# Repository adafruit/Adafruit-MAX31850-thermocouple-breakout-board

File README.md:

# PCB files for Adafruit MAX31850 1-Wire Thermocouple Breakout Board

<a href="http://www.adafruit.com/products/1727"><br/>Click here to purchase one from the Adafruit shop</a>

Thermocouples are very sensitive, requiring a good amplifier with a cold-compensation reference. [So far we've carried the very nice MAX31855 which is an SPI interface thermocouple amplifier](https://www.adafruit.com/products/269). The '855 is great but if you have a lot of thermocouples to measure it isn't terribly easy to use. That's why we are also carrying the new '850 model from Maxim - it's a "1-Wire" thermocouple amp which can have any number of breakouts on a single shared I/O line.

The MAX31850K does everything for you, and can be easily interfaced with any microcontroller that has 1-Wire support. This breakout board has the chip itself, a 3.3V regulator with 10uF bypass capacitors all assembled and tested. This board can be used with 'parasitic power' - where the power is on the data line - or with 'local power' where the power for the converter comes in on the Vin Pin.

Please note: this board does not have level shifting on the 3V Data line - we did this on purpose so that it can be used in parasitic mode. The data line must be level shifted to [3V - our 4-channel shifter works wonderfully for level shifting 1-Wire](http://www.adafruit.com/products/757) and you only need one at the '1-Wire host' for all thermocouples on the shared data line.

The MAX31850K data format is very similar to that of the well known 1-Wire DS18B20 temp sensor but it is not drop in compatible without code changes to check for the new '1 Wire family' type. We have adapted the classic Arduino [OneWire](https://github.com/adafruit/MAX31850_OneWire) and [DallasTemp](https://github.com/adafruit/MAX31850_DallasTemp) libraries to be MAX31850 compatible, so please click on those links to grab our libraries.

Comes with a 2 pin terminal block (for connecting to the thermocouple), 4.7K data line pullup resistor, and pin header (to plug into any breadboard or perfboard).
[Goes great with our 1m K-type thermocouple](http://www.adafruit.com/products/270). Not for use with any other kind of thermocouple, K type only!<Paste>

- Works with any K type thermocouple
- Will not work with any other kind of thermocouple other than K type
- -270C to +1370C output in 0.25 degree increments
- Internal temperature reading
- 3.3 to 5v power supply. Data line is 3V only
- 1-Wire interface allows any number of thermocouple amps on a single data line

Note: The terminal block included with your product may be blue or black.

## License

Adafruit invests time and resources providing this open source design, 
please support Adafruit and open-source hardware by purchasing 
products from Adafruit!

Designed by Limor Fried/Ladyada for Adafruit Industries.
Creative Commons Attribution/Share-Alike, all text above must be included in any redistribution
All text above must be included in any redistribution

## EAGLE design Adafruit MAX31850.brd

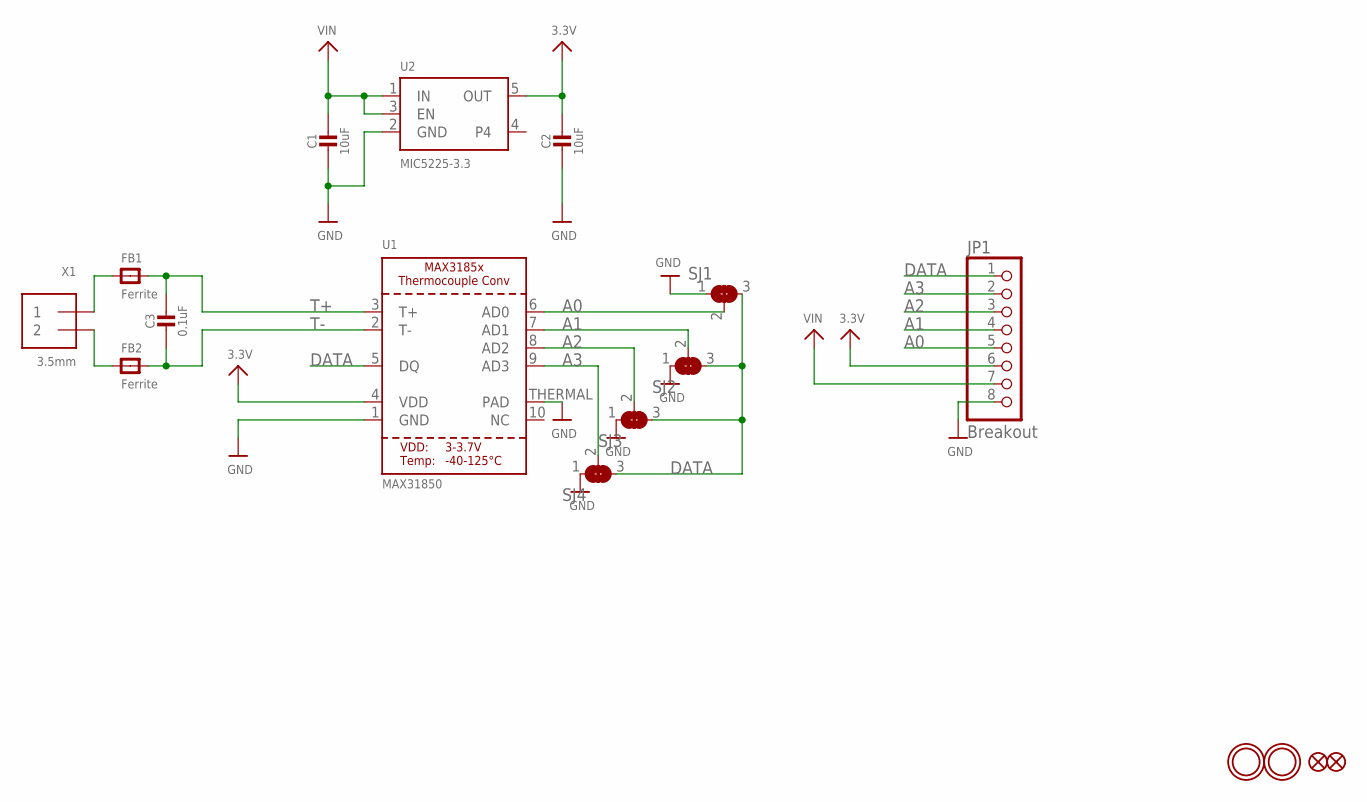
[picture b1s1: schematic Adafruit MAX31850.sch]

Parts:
C1, C2: 10uF; 0805-NO
C3: 0.1uF; 0805-NO
FB1, FB2: Ferrite; 0805
FID1, FID2: FIDUCIAL""; FIDUCIAL_1MM
JP1: Breakout; 1X08_ROUND_70
SJ1, SJ2, SJ3, SJ4: SOLDERJUMPER_2WAY; SOLDERJUMPER_2WAY_OPEN_NOPASTE
U1: MAX31850; TDFN10_3X4MM
U2: MIC5225-3.3; SOT23-5
U$8, U$9: MOUNTINGHOLE2.5; MOUNTINGHOLE_2.5_PLATED
X1: 3.5mm; TERMBLOCK_1X2-3.5MM

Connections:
3.3V: C2.1, JP1.6, U1.4 (VDD), U2.5 (OUT)
A0: JP1.5, SJ1.2, U1.6 (AD0)
A1: JP1.4, SJ2.2, U1.7 (AD1)
A2: JP1.3, SJ3.2, U1.8 (AD2)
A3: JP1.2, SJ4.2, U1.9 (AD3)
DATA: JP1.1, SJ1.3, SJ2.3, SJ3.3, SJ4.3, U1.5 (DQ)
GND: C1.2, C2.2, JP1.8, SJ1.1, SJ2.1, SJ3.1, SJ4.1, U1.1 (GND), U1.THERMAL (PAD), U2.2 (GND)
unnamed: FB1.1, X1.1
unnamed: FB2.1, X1.2
T+: C3.1, FB1.2, U1.3 (T+)
T-: C3.2, FB2.2, U1.2 (T-)
VIN: C1.1, JP1.7, U2.1 (IN), U2.3 (EN)

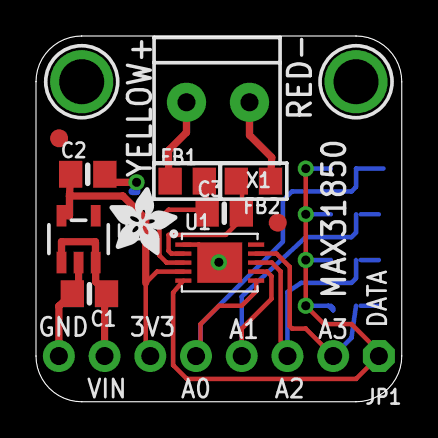
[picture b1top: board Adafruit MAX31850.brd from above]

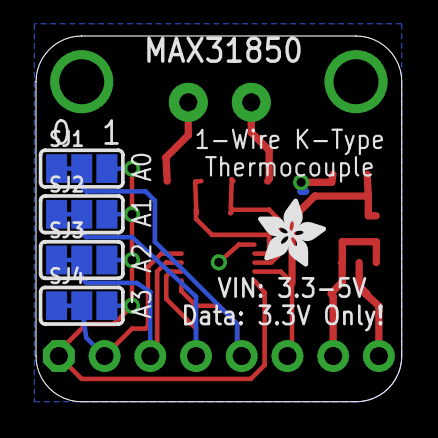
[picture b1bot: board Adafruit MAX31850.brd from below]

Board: 2 copper layers, 20.3 x 20.3 mm, 19 parts (5 on the bottom side), 12 nets.

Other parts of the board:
U$18, U$19: ADAFRUIT_3.5MM

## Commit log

2014-04-28 init
2014-04-28 reeed
2019-05-07 image + readme

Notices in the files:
parts and their libraries:
microbuilder: This work is placed in the public domain, and may be freely used for commercial and non-commercial work with the following conditions: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
